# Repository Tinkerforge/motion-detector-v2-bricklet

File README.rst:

Motion Detector Bricklet 2.0
============================

This repository contains the firmware source code and the hardware design
files. The documentation generator configs can be found at
https://github.com/Tinkerforge/generators

Repository Content
------------------

software/:
 * examples/: Examples for all supported languages
 * build/: Compiled files
 * src/: Source code of firmware
 * Makefile: Makefile to build project

hardware/:
 * Contains KiCad project files and additionally schematics as PDF

datasheets/:
 * Contains datasheets for sensors and complex ICs that are used

Hardware
--------

The hardware is designed with the open source EDA Suite KiCad
(http://www.kicad.org). Before you are able to open the files,
you have to install the Tinkerforge kicad-libraries
(https://github.com/Tinkerforge/kicad-libraries). You can either clone
them directly in hardware/ or clone them in a separate folder and
symlink them into hardware/
(ln -s kicad_path/kicad-libraries project_path/hardware). After that you
can open the .pro file in hardware/ with KiCad and from there view and
modify the schematics and the PCB layout.

Software
--------

If you want to do your own Brick/Bricklet firmware development we highly
recommend that you use our build environment setup script and read the
tutorial (https://www.tinkerforge.com/en/doc/Tutorials/Tutorial_Build_Environment/Tutorial.html).

To compile the C code we recommend you to install the newest GNU Arm Embedded
Toolchain (https://launchpad.net/gcc-arm-embedded/+download).
You also need to install bricklib2 (https://github.com/Tinkerforge/bricklib2).

You can either clone it directly in software/src/ or clone it in a
separate folder and symlink it into software/src/
(ln -s bricklib_path/bricklib2 project_path/software/src/). Finally make sure to
have CMake installed (http://www.cmake.org/cmake/resources/software.html).

After that you can build the firmware by invoking make in software/.
The firmware (.zbin) can then be found in software/build/ and uploaded
with brickv (click button "Flashing" on start screen).

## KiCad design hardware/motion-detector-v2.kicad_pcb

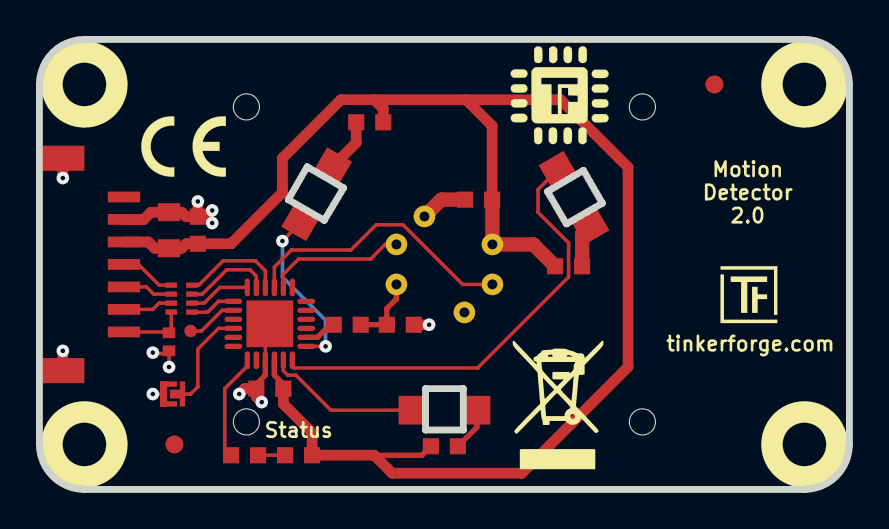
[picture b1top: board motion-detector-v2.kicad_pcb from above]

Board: 2 copper layers, 45.0 x 25.0 mm, 29 parts (0 on the bottom side), 24 nets.

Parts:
C1: 220pF; C0402F
C2: 10uF; C0805
C3: 1uF; C0603F
C4, C6, C7: 100nF; C0603F
D1: blue; D0603F
D2, D3, D4: blue_inv; D1206_INV
Fiducial_Mark: VAL**; Fiducial_Mark
Fiducial_Mark#2: VAL**; Fiducial_Mark
J1: Debug; DEBUG_PAD
P1: CON-SENSOR2
P2: Boot; SolderJumper
R1, R2: 1k; R0603F
R3, R4: 68; R0603F
R5: 22; R0603F
RP1: 82; 4X0402
U1: XMC110024; QFN24-4x4mm-0.5mm
U3: AM612
U4, U5, U6, U7: DRILL; DRILL_NP
VAL: WEEE_7mm
VAL#2: CE_5mm

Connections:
ENABLE: U1.20, U3.2
GND: C1.1, C2.1, C3.1, C4.1, C6.1, C7.1, P1.2, P1.EP, P2.1, U1.9, U1.EXP, U3.3, U3.6
LED_BTM: D4.2, U1.11
LED_TOP_L: D2.2, U1.13
LED_TOP_R: D3.2, U1.12
unnamed: C1.2, P1.7, RP1.4
unnamed: D1.2, R1.2
unnamed: D2.1, R3.1
unnamed: D3.1, R4.1
unnamed: D4.1, R5.1
unnamed: J1.1, U1.2
unnamed: P1.4, RP1.1
unnamed: P1.5, RP1.2
unnamed: P1.6, RP1.3
unnamed: P2.2, U1.4
unnamed: R1.1, U1.7
unnamed: R2.1, U1.14
S-CLK: RP1.7, U1.23
S-CS: RP1.8, U1.22
S-MISO: RP1.5, U1.1
S-MOSI: RP1.6, U1.24
VCC: C2.2, C3.2, C4.2, C7.2, D1.1, P1.3, R3.2, R4.2, R5.2, U1.10, U3.4
VOUT: U1.21, U3.5
VSENS: C6.2, R2.2, U3.1

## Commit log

2017-09-05 Add datasheets
2017-09-05 add hardware files of motion detector 2.0
2017-09-05 add cutouts for leds
2017-09-29 fix ams612 routing, change led positions
2017-10-04 Add mcp4018, am612 + led drivers and communication implementation
2017-10-19 version without i2c poti, uses rc circuit
2017-10-19 fix status led text
2017-10-25 change rgb leds to 3x blue
2017-10-25 Use PWM as voltage source, remove mcp4018 i2c poti
2017-10-25 Change naming for all blue LEDs instead of RGB
2017-10-26 specify prozessor type
2017-10-27 Turn logging off
2018-01-11 Add examples
2018-01-15 Remove unused ICs and lenses to avoid confusion
2018-02-02 Add first set of examples
2018-02-15 Fix edge cuts
2018-02-15 Add 3d information (final)
2018-02-15 Add 3d model (*.step & *.FCStd)
2018-02-16 Add schematic (PDF)
2018-02-19 add cutout information
2018-02-19 javascript: Close div tag correctly
2018-02-20 Cleanup KiCad libraries config
    Ensure LibDir=kicad-libraries and LibName1=tinkerforge.
    Remove special library.
2018-02-28 Add new 3d model with more detailed components
2018-03-05 Remove unused flash-size define
2018-05-11 Rename files
2018-05-24 perl: Use strict in examples
2018-06-18 Change capacitor footprint(s) to C0402F
2018-06-28 Fix readme
2018-07-06 Add LabVIEW examples
2018-07-11 Add Makefile with docker support
2018-07-11 Remove obsolete generate_makefile scripts
2018-07-11 Update directory structure and build instructions
2018-10-04 Increase version for new release (changes in bricklib2)
2018-10-04 Add rev to changelog
2018-11-06 Add rust examples
2018-11-07 rust: Accept host names for ip connection, fix naming inconsistencies
2018-11-07 rust: Rename callback receivers.
2018-12-14 Add go examples.
2018-12-18 go: Change import path.
2018-12-18 go: Change import path again.
2018-12-20 rust: Reformat examples.
2019-01-21 fix status text, add bottom copper masking for sensor
2019-01-24 mqtt: Add examples.
2019-01-24 mqtt: Fix example header.
2019-01-24 mqtt: Remove executable bit in example permissions.
2019-01-24 go: Minor example fixes.
2019-01-24 mqtt: Minor example fixes.
2019-05-14 Update rust examples.
2019-08-22 c: Adapt to bindings changes
2020-01-13 examples: Use python3 input instead of python2 raw_input.
2020-01-13 examples: mqtt: Remove trailing whitespace.
2020-03-16 Whitespace
2020-04-07 examples: rust: Always block when calling bindings functions.
2020-08-19 Add uc examples.
2020-08-25 uc: Fix whitespace
2020-08-27 uc: Fix warnings.
2020-09-02 uc: Add example driver note.
2021-10-25 Update KiCad link
    https://www.kicad.org/blog/2021/10/Avoid-links-to-former-kicad-domain/
2022-04-19 examples: uc: Rename TF_HalContext to TF_HAL.
2022-04-27 uc: Adapt to bindings changes
2022-07-06 Add license files.

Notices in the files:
hardware/motion-detector-v2.kicad_pcb:
Licensed under CERN OHL v.1.1
Copyright (©) 2017, B.Nordmeyer
Copyright Tinkerforge GmbH 2017.
This documentation describes Open Hardware and is licensed under the
CERN OHL v. 1.1.
